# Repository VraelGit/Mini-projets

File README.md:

# Mini-projets

Tout les mini projets + codes source

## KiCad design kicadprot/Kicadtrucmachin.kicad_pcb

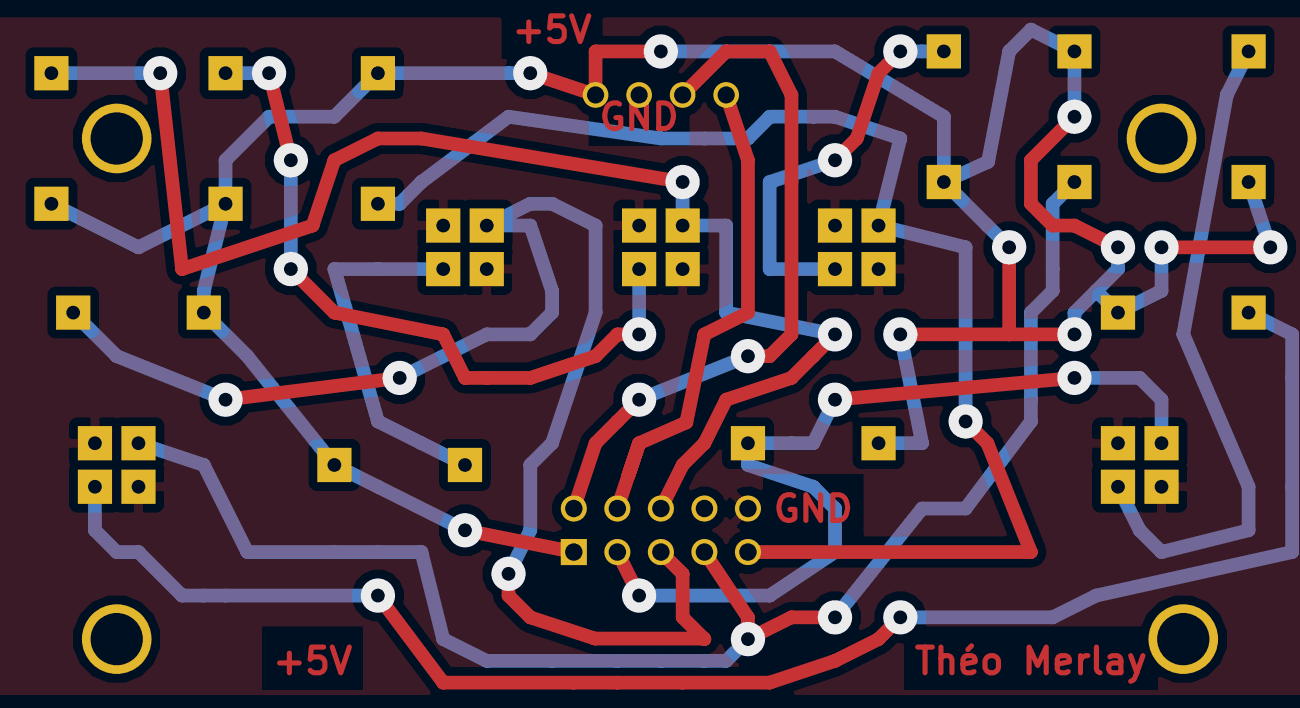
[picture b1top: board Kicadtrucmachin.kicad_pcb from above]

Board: 2 copper layers, 21 parts (0 on the bottom side), 14 nets.

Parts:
1PIN, 1PIN#2, 1PIN#3, 1PIN#4: P***; 1pin
IC1, IC2, IC3, IC4, IC5: CNY70
P1: CONN_4; PIN_ARRAY_4x1
P2: CONN_5X2; PIN_ARRAY_5x2
R1, R2, R3, R4, R5, R7, R8, R9, R10, R12: R; R3

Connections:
+5V: P1.1, P2.1, R1.1, R2.1, R3.1, R4.1, R5.1, R7.2, R8.2, R9.2, R10.2, R12.2
/AN0: IC4.3, P2.3, R12.1
/AN1: IC3.3, P2.5, R9.1
/AN2: IC2.3, P2.7, R8.1
/AN3: IC1.3, P2.9, R7.1
/D0: IC5.3, P2.6, R10.1
GND: IC1.2, IC1.4, IC2.2, IC2.4, IC3.2, IC3.4, IC4.2, IC4.4, IC5.2, IC5.4, P1.2, P2.10
unnamed: IC2.1, R2.2
unnamed: IC4.1, R4.2
unnamed: IC1.1, R1.2
unnamed: IC5.1, R5.2
unnamed: IC3.1, R3.2
unnamed: P1.3, P2.2
unnamed: P1.4, P2.4
